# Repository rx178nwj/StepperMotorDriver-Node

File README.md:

# StepperMotorDriver-Node

NEMA17 用 / NEMA23 用のステッピングモータードライバー基板と、そのファームウェアのリポジトリです。
基板をモーター背面に取り付け、CAN バス経由で制御するノードとして使います。

## ディレクトリ構成

| パス | 内容 |
|------|------|
| `schematic_NEMA17/` | NEMA17 用基板の KiCad プロジェクト（回路図・基板・Gerber など） |
| `schematic_NEMA23/` | NEMA23 用基板の KiCad プロジェクト（回路図・基板・Gerber など） |
| `firmware/` | ファームウェア（STM32L433、CMake ベース。詳細は `firmware/README.md`） |
| `docs/` | ドキュメント |
| `datasheet/` | 部品データシート置き場（本体は含まない。`datasheet/README.md` 参照） |

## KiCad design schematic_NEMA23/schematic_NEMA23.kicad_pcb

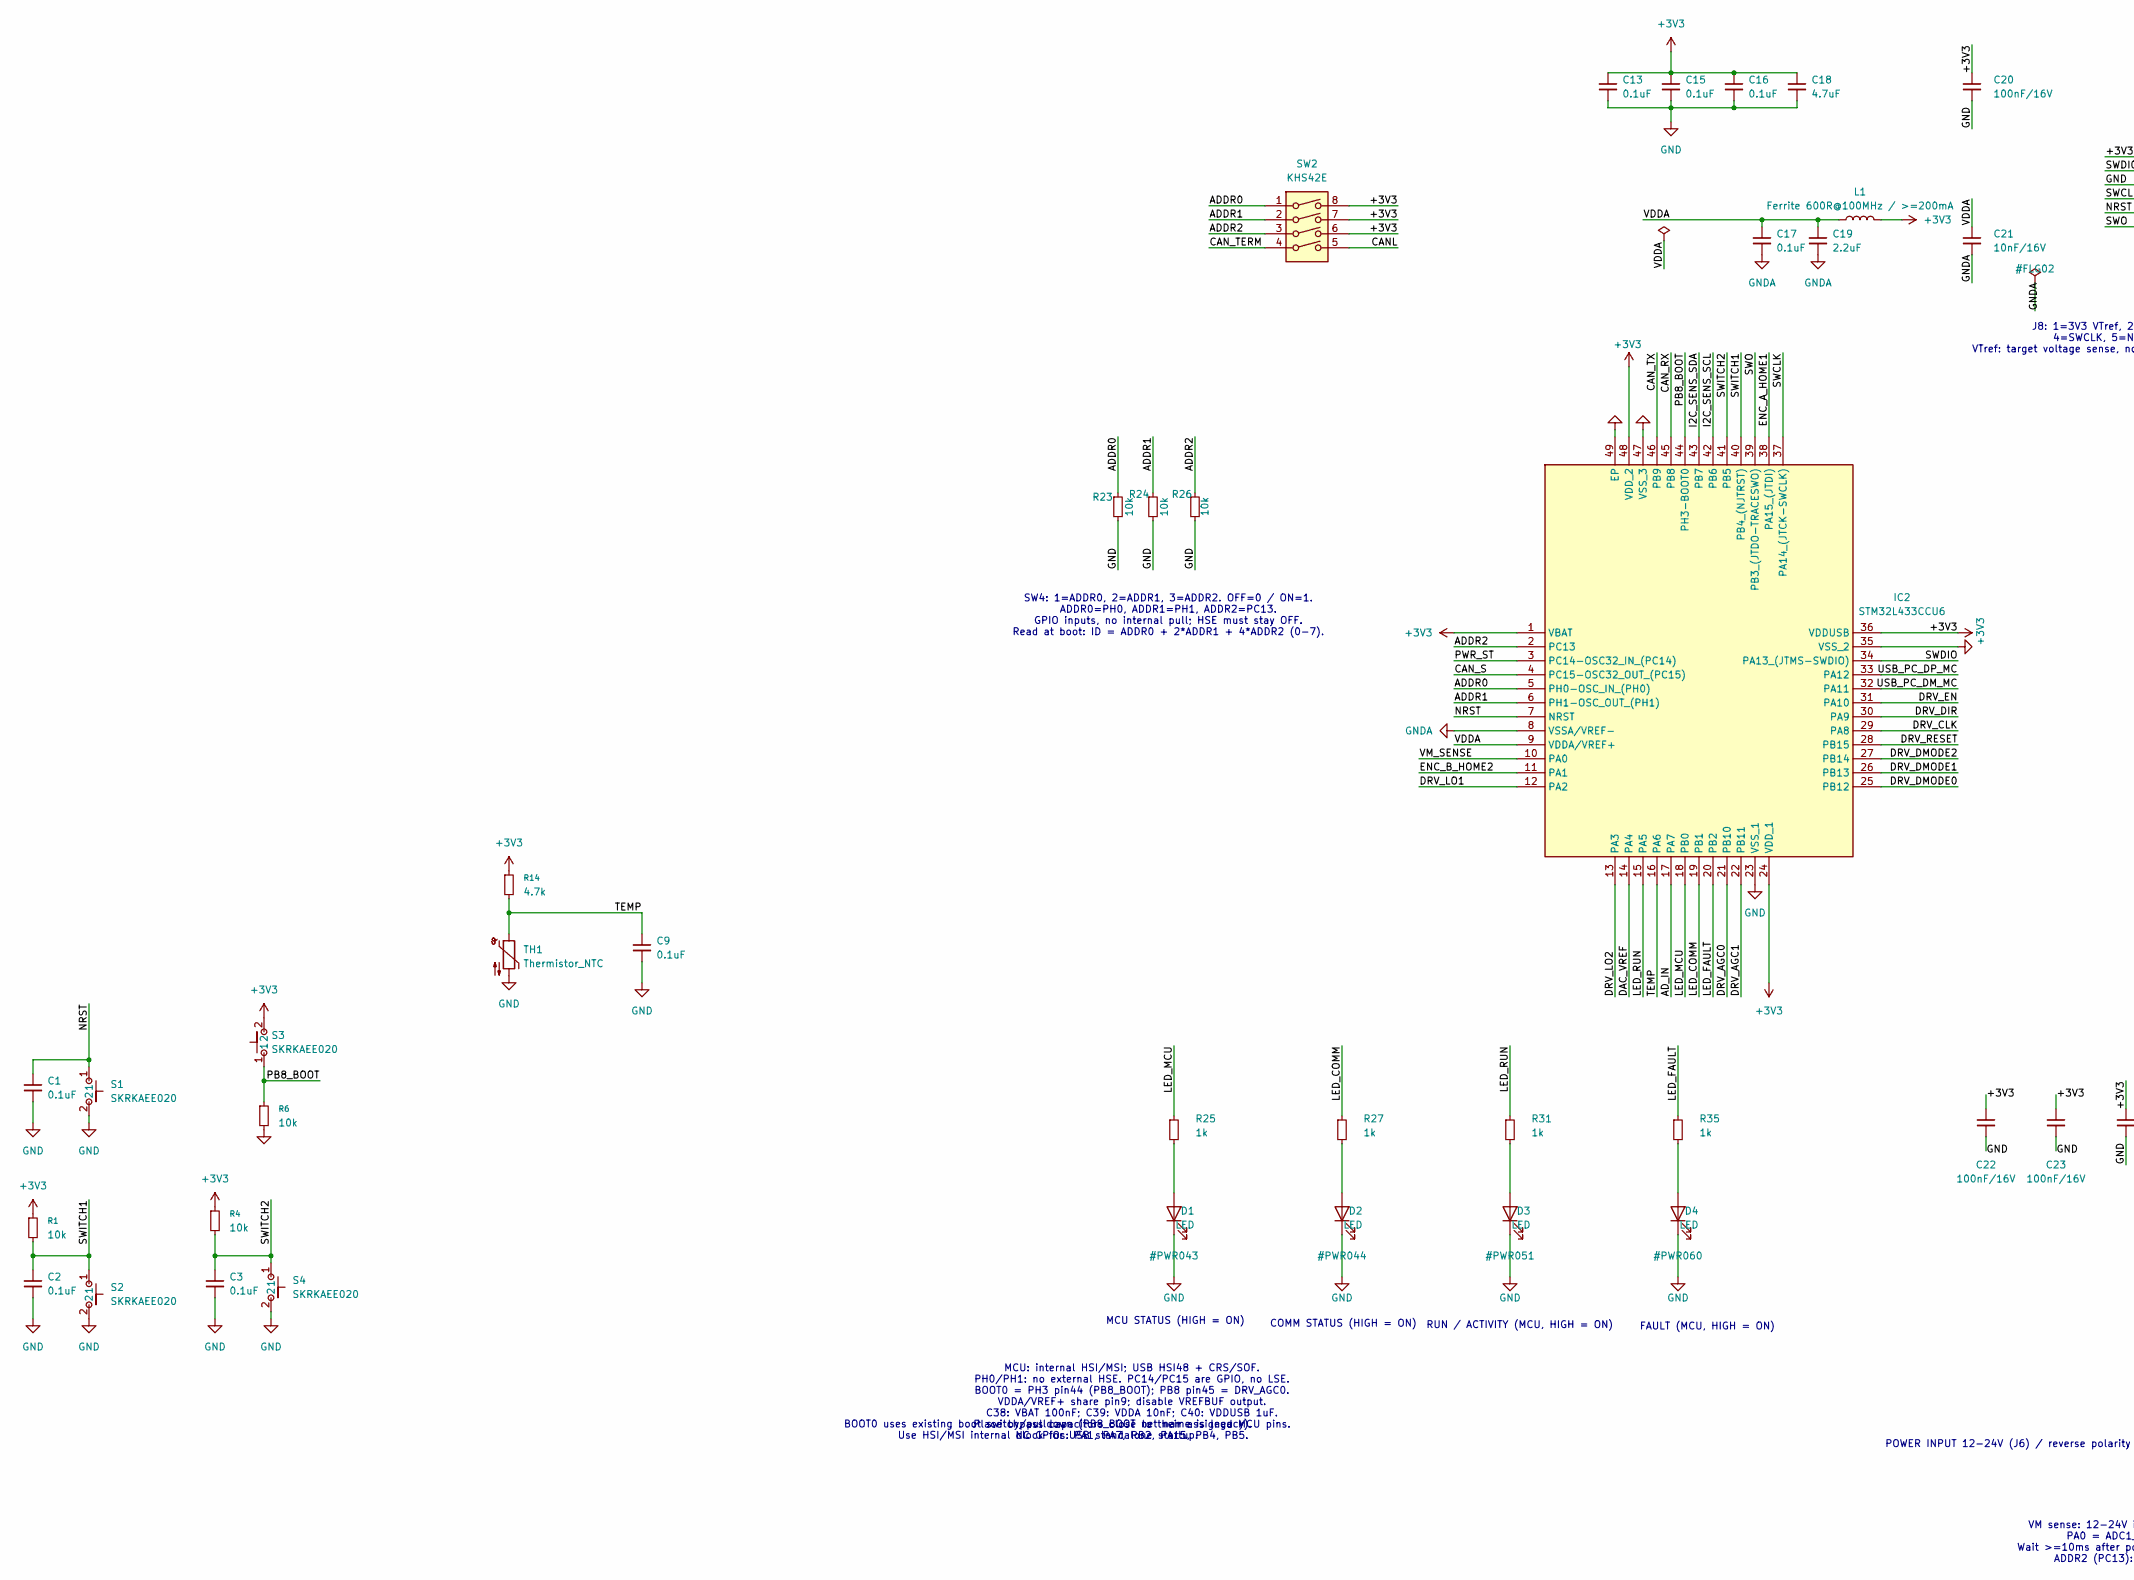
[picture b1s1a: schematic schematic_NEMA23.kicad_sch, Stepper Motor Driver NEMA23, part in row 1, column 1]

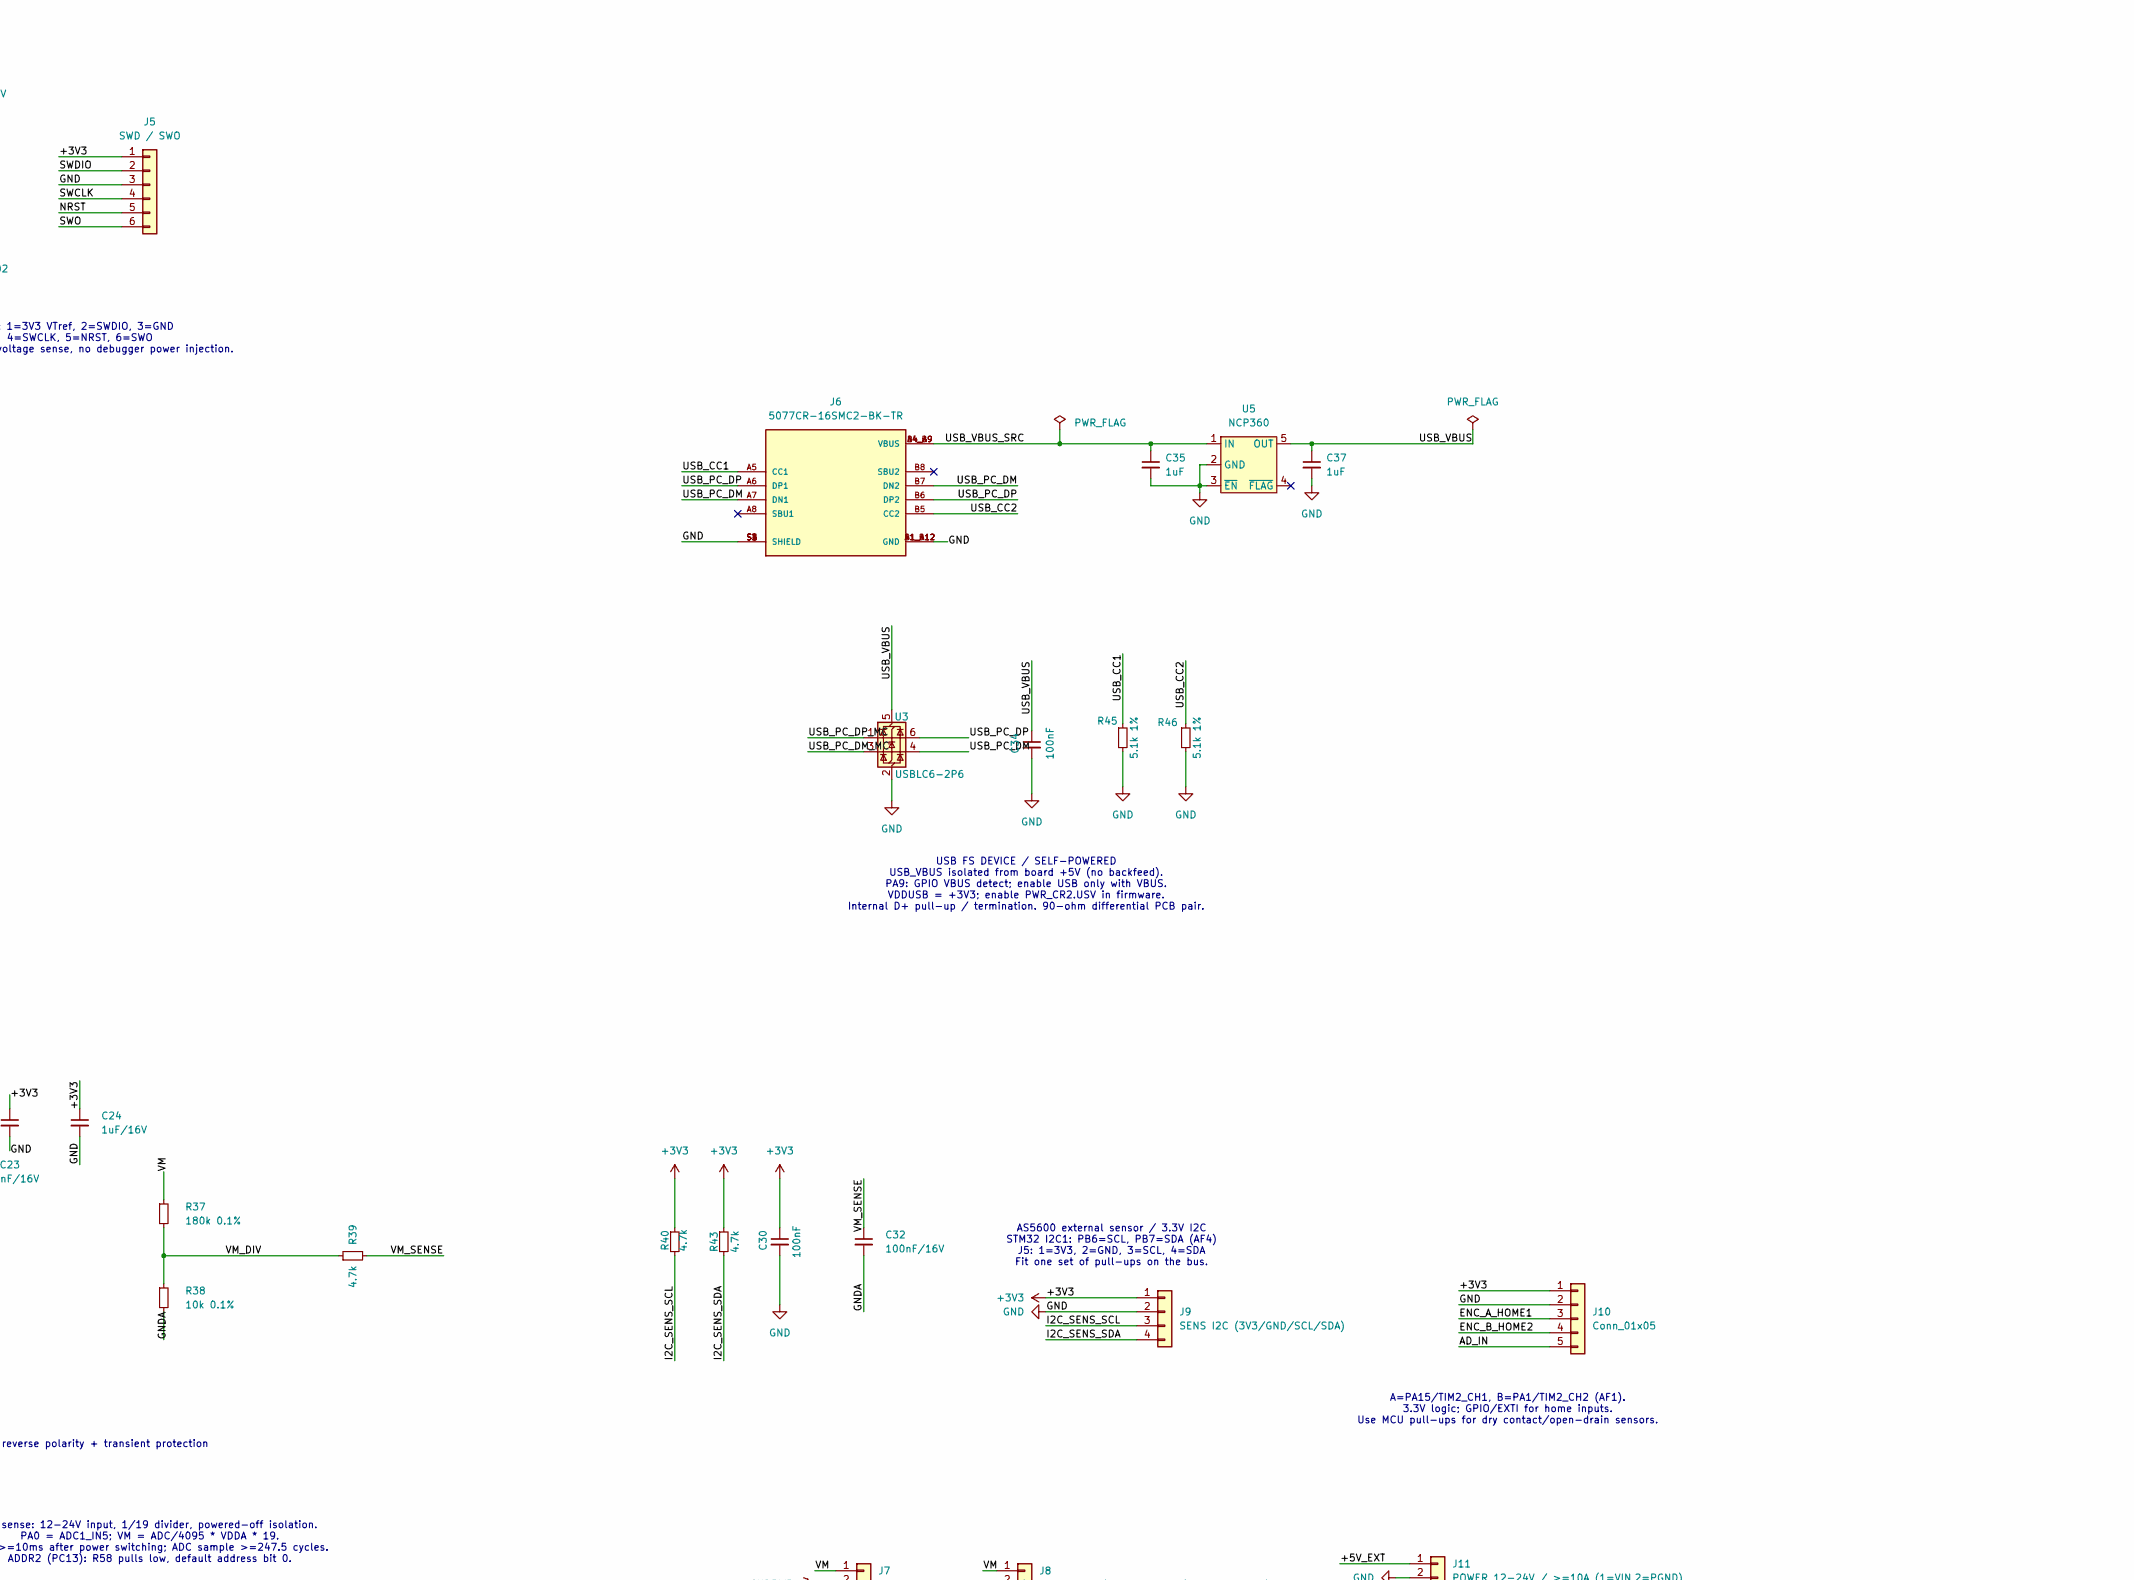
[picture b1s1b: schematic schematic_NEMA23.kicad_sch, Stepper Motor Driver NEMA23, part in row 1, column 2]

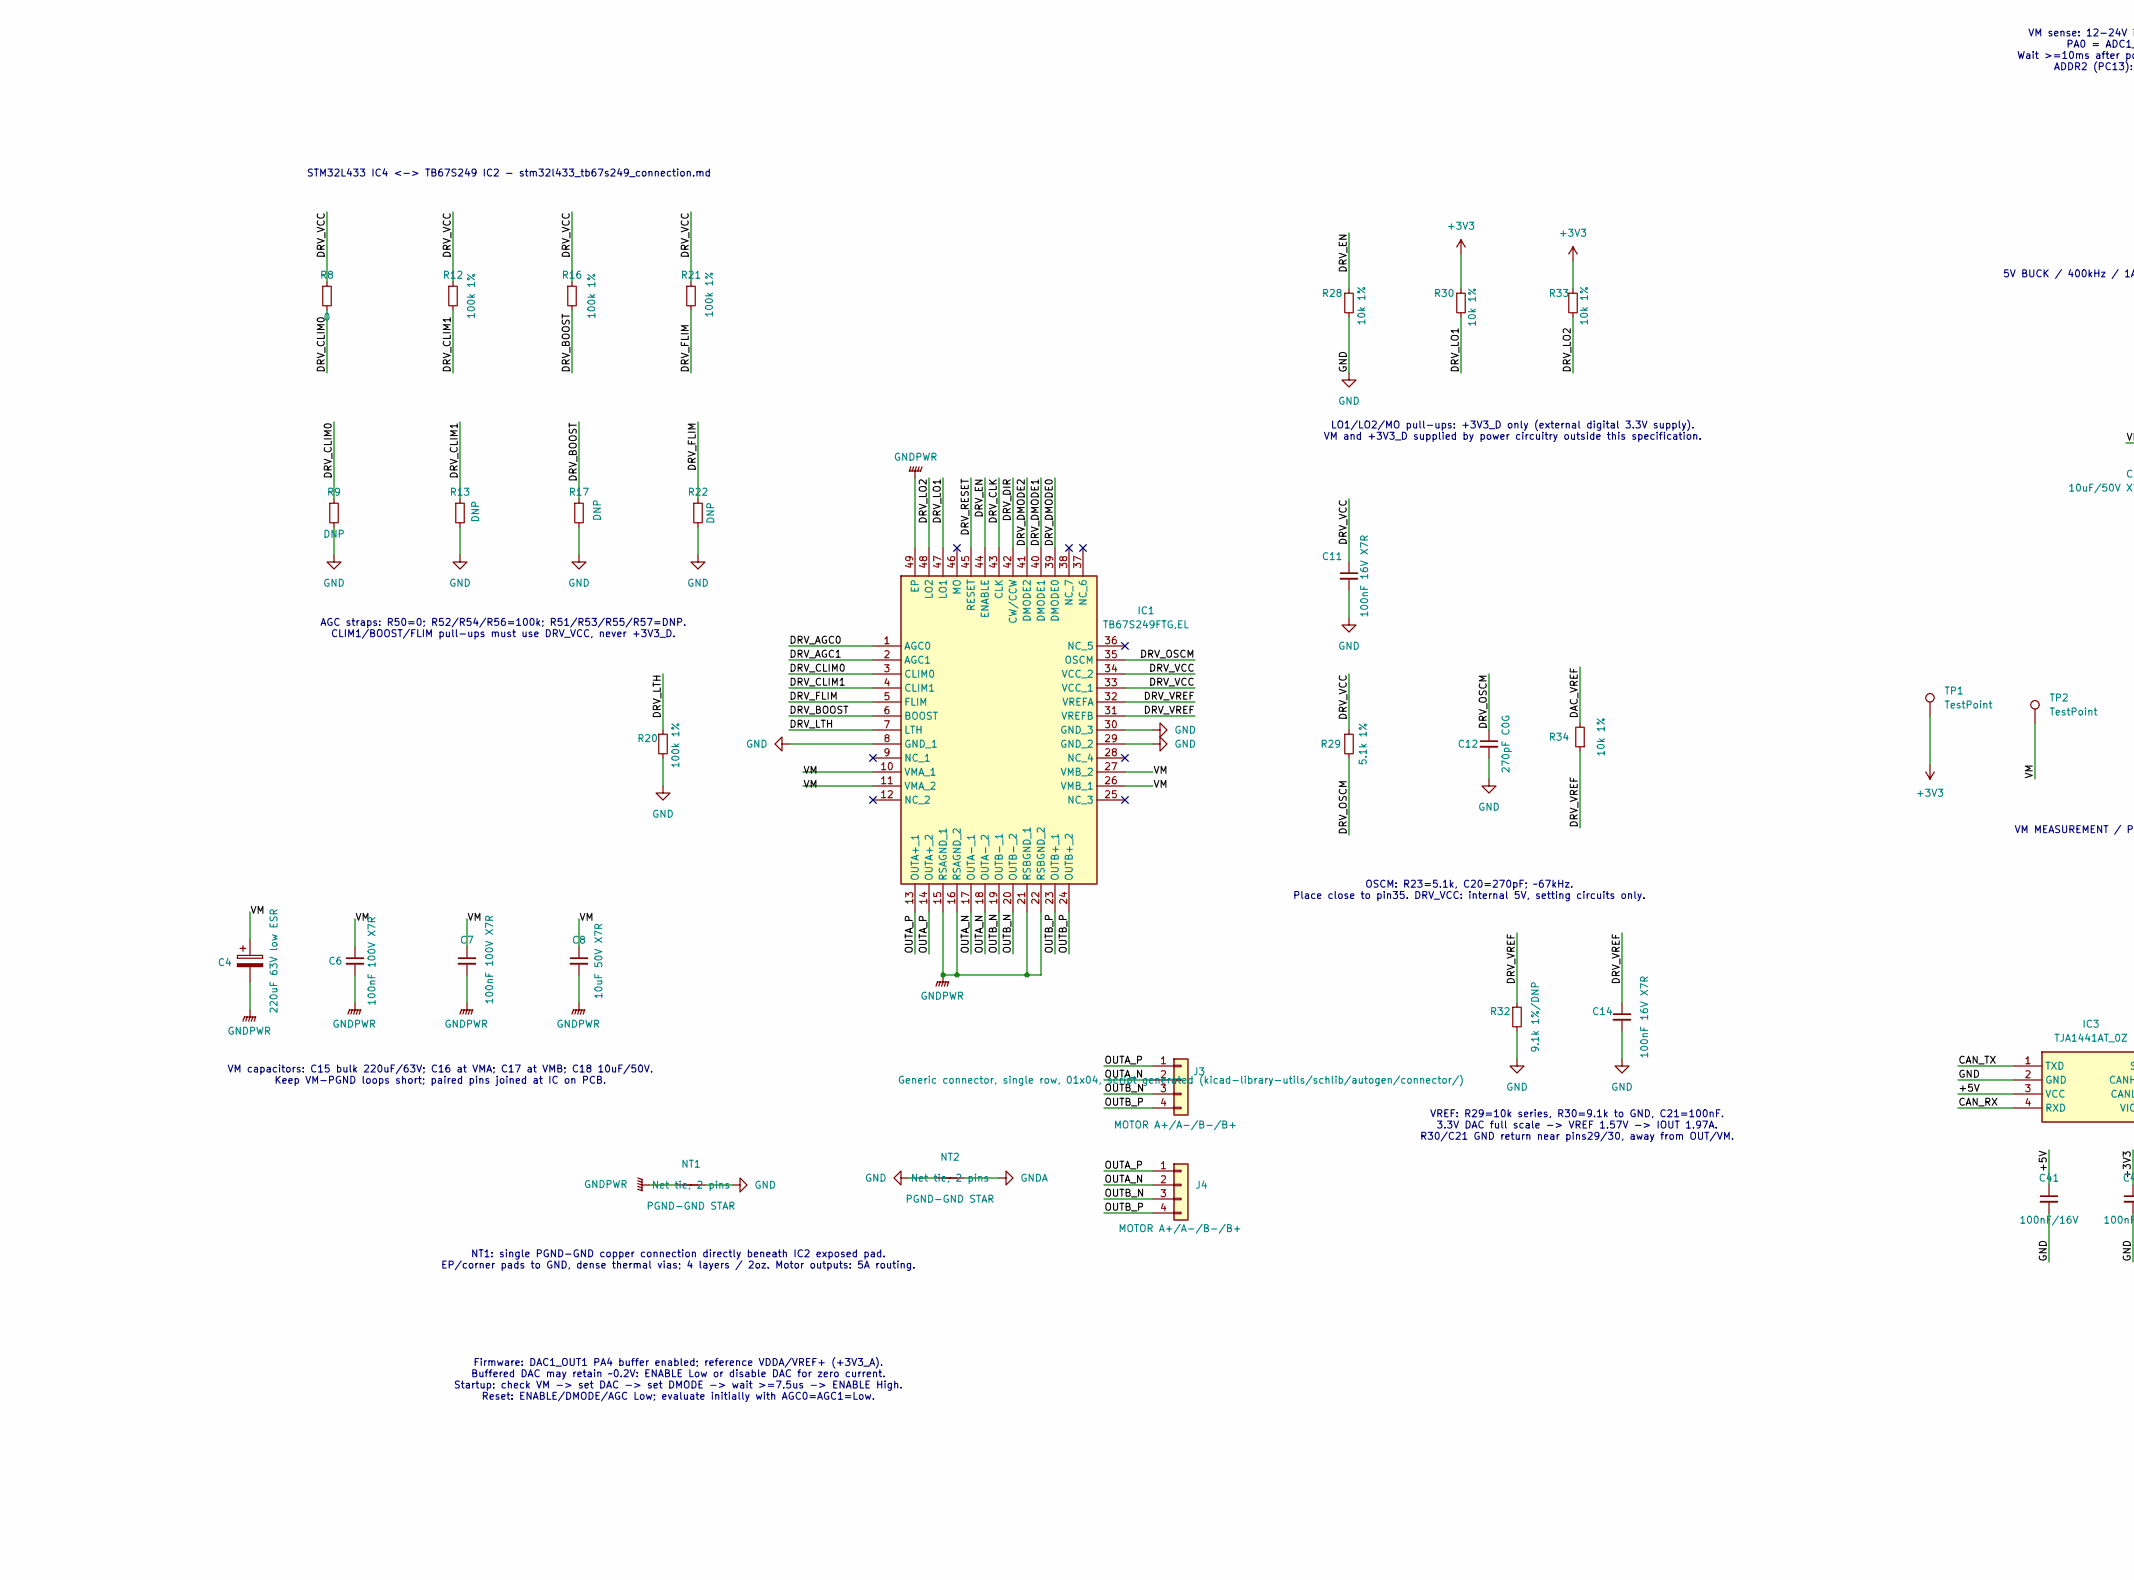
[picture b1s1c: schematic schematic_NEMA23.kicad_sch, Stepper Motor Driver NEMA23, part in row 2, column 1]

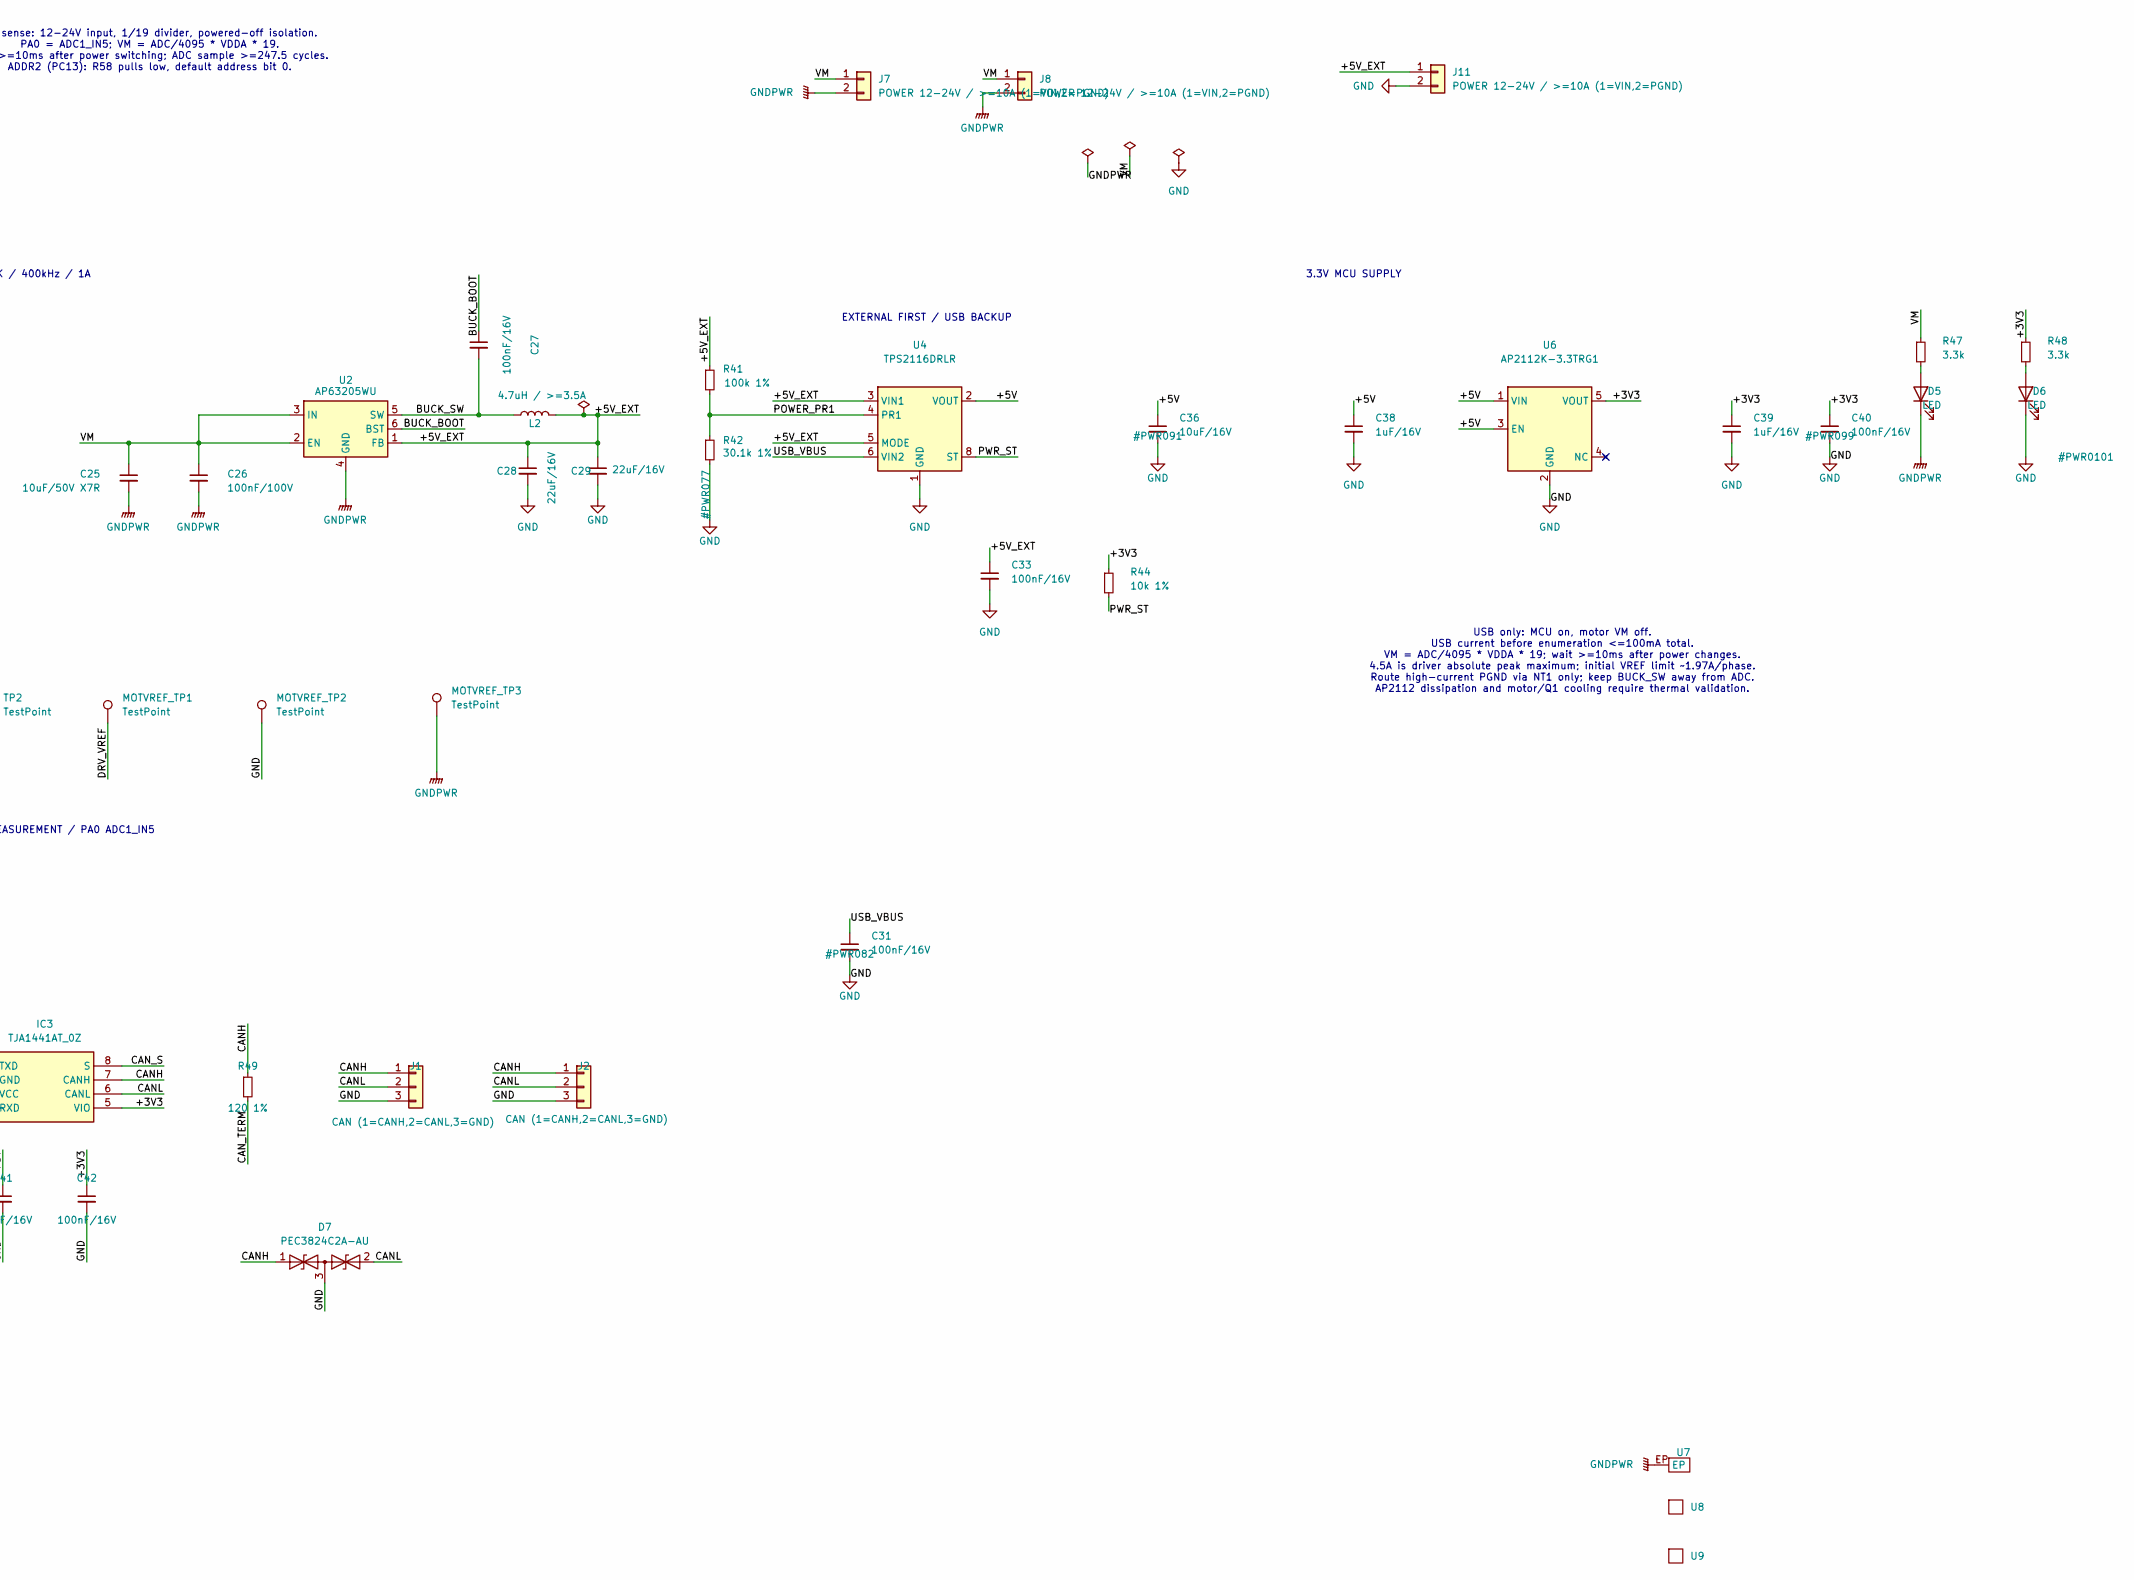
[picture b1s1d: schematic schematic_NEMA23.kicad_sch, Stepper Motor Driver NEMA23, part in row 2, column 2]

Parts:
C1, C2, C3, C9: 0.1uF; R_0402_1005Metric
C4: 220uF 63V low ESR; CP_Radial_D10.0mm_P5.00mm
C6, C7: 100nF 100V X7R; C_0603_1608Metric
C8: 10uF 50V X7R; C_0805_2012Metric
C11, C14: 100nF 16V X7R; C_0402_1005Metric
C12: 270pF C0G; C_0402_1005Metric
C13, C15, C16: 0.1uF; R_0603_1608Metric
C17: 0.1uF; C_0603_1608Metric
C18: 4.7uF; C_0805_2012Metric
C19: 2.2uF; C_0603_1608Metric
C20, C22, C23, C31, C33, C40: 100nF/16V; C_0603_1608Metric
C21: 10nF/16V; C_0603_1608Metric
C24, C38, C39: 1uF/16V; C_0603_1608Metric
C25: 10uF/50V X7R; C_0805_2012Metric; Voltage 50V
C26: 100nF/100V; C_0603_1608Metric
C27: 100nF/16V; C_0805_2012Metric
C28, C29: 22uF/16V; C_0805_2012Metric
C30, C34: 100nF; C_0603_1608Metric
C32: 100nF/16V; R_0402_1005Metric
C35, C37: 1uF; C_0603_1608Metric
C36: 10uF/16V; C_0805_2012Metric
C41, C42: 100nF/16V; C_0402_1005Metric
D1, D2, D3, D4, D5, D6: LED; LED_0603_1608Metric
D7: PEC3824C2A-AU; SOT-23
IC1: TB67S249FTG,EL; QFN50P700X700X100-49N-D; Mouser Part Number 757-TB67S249FTGEL
IC2: STM32L433CCU6; QFN50P700X700X60-49N-D; Mouser Part Number 511-STM32L433CCU6
IC3: TJA1441AT_0Z; SOIC127P600X175-8N; Mouser Part Number 771-TJA1441AT/0Z
J1, J2: CAN (1=CANH,2=CANL,3=GND); JST_PH_B3B-PH-K_1x03_P2.00mm_Vertical; MPN B3B-PH-K-S
J3: MOTOR A+/A-/B-/B+; JST_XH_B4B-XH-A_1x04_P2.50mm_Vertical
J4: MOTOR A+/A-/B-/B+; 名称未設定_1
J5: SWD / SWO; JST_ZH_B6B-ZR_1x06_P1.50mm_Vertical
J6: 5077CR-16SMC2-BK-TR; NELTRON_5077CR-16SMC2-BK-TR; PARTREV B
J7: POWER 12-24V / >=10A (1=VIN,2=PGND); Conn_VM
J8: POWER 12-24V / >=10A (1=VIN,2=PGND); JST_VH_B2P-VH_1x02_P3.96mm_Vertical
J9: SENS I2C (3V3/GND/SCL/SDA); JST_PH_B4B-PH-K_1x04_P2.00mm_Vertical
J10: Conn_01x05; JST_ZH_B5B-ZR_1x05_P1.50mm_Vertical
J11: POWER 12-24V / >=10A (1=VIN,2=PGND); JST_PH_B2B-PH-K_1x02_P2.00mm_Vertical
L1: Ferrite 600R@100MHz / >=200mA; L_0603_1608Metric
L2: 4.7uH / >=3.5A; INDPM5552X300N; MPN XAL6060-472MEC
MOTVREF_TP1, MOTVREF_TP2: TestPoint; TestPoint_THTPad_D2.0mm_Drill1.0mm
MOTVREF_TP3: TestPoint; TestPoint_Pad_D1.5mm
NT1, NT2: PGND-GND STAR; NetTie-2_SMD_Pad0.5mm
R1, R4, R6, R23, R24, R26: 10k; R_0402_1005Metric
R8: 0; R_0402_1005Metric
R9, R13, R17, R22: DNP; R_0402_1005Metric
R12, R16, R20, R21: 100k 1%; R_0402_1005Metric
R14, R39, R40, R43: 4.7k; R_0402_1005Metric
R25, R27, R31, R35: 1k; R_0603_1608Metric
R28, R30, R33, R34, R44: 10k 1%; R_0402_1005Metric
R29, R45, R46: 5.1k 1%; R_0402_1005Metric
R32: 9.1k 1%/DNP; R_0402_1005Metric
R37: 180k 0.1%; R_0603_1608Metric
R38: 10k 0.1%; R_0603_1608Metric
R41: 100k 1%; R_0603_1608Metric
R42: 30.1k 1%; R_0603_1608Metric
R47, R48: 3.3k; R_0603_1608Metric
R49: 120 1%; R_0603_1608Metric
S1, S2, S3, S4: SKRKAEE020; Mouser Part Number 688-SKRKAEE020
SW2: KHS42E; SOIC-8_5.3x6.2mm_P1.27mm
TH1: Thermistor_NTC; R_0603_1608Metric
TP1, TP2: TestPoint; TestPoint_Pad_D1.5mm
U2: AP63205WU; TSOT-23-6; MPN AP63205WU-7
U3: USBLC6-2P6; SOT-666
U4: TPS2116DRLR; SOT-583-8; MPN TPS2116DRLR
U5: NCP360; TSOP-5_1.65x3.05mm_P0.95mm
U6: AP2112K-3.3TRG1; SOT-23-5; MPN AP2112K-3.3TRG1
U7: サーマルパッド
U8: MainBoard
U9: ヒートシンク30x30

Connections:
+3V3: C13.1, C15.1, C16.1, C18.1, C20.1, C22.1, C23.1, C24.1, C30.1, C39.1, C40.1, C42.1, IC2.1 (VBAT), IC2.24 (VDD_1), IC2.36 (VDDUSB), IC2.48 (VDD_2), IC3.5 (VIO), J5.1, J9.1, J10.1, L1.2, R1.1, R4.1, R14.1, R30.1, R33.1, R40.1, R43.1, R44.1, R48.1, S3.2, SW2.6, SW2.7, SW2.8, TP1.1 (1_1), U6.5 (VOUT)
/+5V: C36.1, C38.1, C41.1, IC3.3 (VCC), U4.2 (VOUT), U4.7 (VOUT), U6.1 (VIN), U6.3 (EN)
/+5V_EXT: C28.1, C29.1, C33.1, J11.1, L2.2, R41.1, U2.1 (FB), U4.3 (VIN1), U4.5 (MODE)
/ADDR0: IC2.5 (PH0-OSC_IN_(PH0)), R23.1, SW2.1
/ADDR1: IC2.6 (PH1-OSC_OUT_(PH1)), R24.1, SW2.2
/ADDR2: IC2.2 (PC13), R26.1, SW2.3
/AD_IN: IC2.17 (PA7), J10.5
/BUCK_BOOT: C27.1, U2.6 (BST)
/BUCK_SW: C27.2, L2.1, U2.5 (SW)
/CANH: D7.1 (A1), IC3.7 (CANH), J1.1, J2.1, R49.1
/CANL: D7.2 (A2), IC3.6 (CANL), J1.2, J2.2, SW2.5
/CAN_RX: IC2.45 (PB8), IC3.4 (RXD)
/CAN_S: IC2.4 (PC15-OSC32_OUT_(PC15)), IC3.8 (S)
/CAN_TERM: R49.2, SW2.4
/CAN_TX: IC2.46 (PB9), IC3.1 (TXD)
/DAC_VREF: IC2.14 (PA4), R34.2
/DRV_AGC0: IC1.1 (AGC0), IC2.21 (PB10)
/DRV_AGC1: IC1.2 (AGC1), IC2.22 (PB11)
/DRV_BOOST: IC1.6 (BOOST), R16.2, R17.1
/DRV_CLIM0: IC1.3 (CLIM0), R8.2, R9.1
/DRV_CLIM1: IC1.4 (CLIM1), R12.2, R13.1
/DRV_CLK: IC1.43 (CLK), IC2.29 (PA8)
/DRV_DIR: IC1.42 (CW/CCW), IC2.30 (PA9)
/DRV_DMODE0: IC1.39 (DMODE0), IC2.25 (PB12)
/DRV_DMODE1: IC1.40 (DMODE1), IC2.26 (PB13)
/DRV_DMODE2: IC1.41 (DMODE2), IC2.27 (PB14)
/DRV_EN: IC1.44 (ENABLE), IC2.31 (PA10), R28.1
/DRV_FLIM: IC1.5 (FLIM), R21.2, R22.1
/DRV_LO1: IC1.47 (LO1), IC2.12 (PA2), R30.2
/DRV_LO2: IC1.48 (LO2), IC2.13 (PA3), R33.2
/DRV_LTH: IC1.7 (LTH), R20.1
/DRV_OSCM: C12.1, IC1.35 (OSCM), R29.2
/DRV_RESET: IC1.45 (RESET), IC2.28 (PB15)
/DRV_VCC: C11.1, IC1.33 (VCC_1), IC1.34 (VCC_2), R8.1, R12.1, R16.1, R21.1, R29.1
/DRV_VREF: C14.1, IC1.31 (VREFB), IC1.32 (VREFA), MOTVREF_TP1.1 (1_1), R32.1, R34.1
/ENC_A_HOME1: IC2.38 (PA15_(JTDI)), J10.3
/ENC_B_HOME2: IC2.11 (PA1), J10.4
/I2C_SENS_SCL: IC2.42 (PB6), J9.3, R40.2
/I2C_SENS_SDA: IC2.43 (PB7), J9.4, R43.2
/LED_COMM: IC2.19 (PB1), R27.1
/LED_FAULT: IC2.20 (PB2), R35.1
/LED_MCU: IC2.18 (PB0), R25.1
/LED_RUN: IC2.15 (PA5), R31.1
/NRST: C1.1, IC2.7 (NRST), J5.5, S1.1
/OUTA_N: IC1.17 (OUTA-_1), IC1.18 (OUTA-_2), J3.2, J4.2
/OUTA_P: IC1.13 (OUTA+_1), IC1.14 (OUTA+_2), J3.1, J4.1
/OUTB_N: IC1.19 (OUTB-_1), IC1.20 (OUTB-_2), J3.3, J4.3
/OUTB_P: IC1.23 (OUTB+_1), IC1.24 (OUTB+_2), J3.4, J4.4
/PB8_BOOT: IC2.44 (PH3-BOOT0), R6.1, S3.1
/POWER_PR1: R41.2, R42.1, U4.4 (PR1)
/PWR_ST: IC2.3 (PC14-OSC32_IN_(PC14)), R44.2, U4.8 (ST)
/SWCLK: IC2.37 (PA14_(JTCK-SWCLK)), J5.4
/SWDIO: IC2.34 (PA13_(JTMS-SWDIO)), J5.2
/SWITCH1: C2.1, IC2.40 (PB4_(NJTRST)), R1.2, S2.1
/SWITCH2: C3.1, IC2.41 (PB5), R4.2, S4.1
/SWO: IC2.39 (PB3_(JTDO-TRACESWO)), J5.6
/TEMP: C9.1, IC2.16 (PA6), R14.2, TH1.1
/USB_CC1: J6.A5 (CC1), R45.1
/USB_CC2: J6.B5 (CC2), R46.1
/USB_PC_DM: J6.A7 (DN1), J6.B7 (DN2), U3.4 (I/O2)
/USB_PC_DM_MC: IC2.32 (PA11), U3.3 (I/O2)
/USB_PC_DP: J6.A6 (DP1), J6.B6 (DP2), U3.6 (I/O1)
/USB_PC_DP_MC: IC2.33 (PA12), U3.1 (I/O1)
/USB_VBUS: C31.1, C34.1, C37.1, U3.5 (VBUS), U4.6 (VIN2), U5.5 (OUT)
/USB_VBUS_SRC: C35.1, J6.A4_B9 (VBUS), J6.B4_A9 (VBUS), U5.1 (IN)
/VDDA: C17.1, C19.1, C21.1, IC2.9 (VDDA/VREF+), L1.1
/VM: C4.1, C6.1, C7.1, C8.1, C25.1, C26.1, IC1.10 (VMA_1), IC1.11 (VMA_2), IC1.26 (VMB_1), IC1.27 (VMB_2), J7.1, J8.1, R37.1, R47.1, TP2.1 (1_1), U2.2 (EN), U2.3 (IN)
/VM_DIV: R37.2, R38.1, R39.1
/VM_SENSE: C32.1, IC2.10 (PA0), R39.2
GND: C1.2, C2.2, C3.2, C9.2, C11.2, C12.2, C13.2, C14.2, C15.2, C16.2, C18.2, C20.2, C22.2, C23.2, C24.2, C28.2, C29.2, C30.2, C31.2, C33.2, C34.2, C35.2, C36.2, C37.2, C38.2, C39.2, C40.2, C41.2, C42.2, D1.1 (K), D2.1 (K), D3.1 (K), D4.1 (K), D6.1 (K), D7.3 (common), IC1.8 (GND_1), IC1.29 (GND_2), IC1.30 (GND_3), IC2.23 (VSS_1), IC2.35 (VSS_2), IC2.47 (VSS_3), IC2.49 (EP), IC3.2 (GND), J1.3, J2.3, J5.3, J6.A1_B12 (GND), J6.B1_A12 (GND), J6.S1 (SHIELD), J6.S2 (SHIELD), J6.S3 (SHIELD), J6.S4 (SHIELD), J9.2, J10.2, J11.2, MOTVREF_TP2.1 (1_1), NT1.2, NT2.1, R6.2, R9.2, R13.2, R17.2, R20.2, R22.2, R23.2, R24.2, R26.2, R28.2, R32.2, R42.2, R45.2, R46.2, S1.2, S2.2, S4.2, TH1.2, U3.2 (GND), U4.1 (GND), U5.2 (GND), U5.3 (~EN), U6.2 (GND)
GNDA: C17.2, C19.2, C21.2, C32.2, IC2.8 (VSSA/VREF-), NT2.2, R38.2
GNDPWR: C4.2, C6.2, C7.2, C8.2, C25.2, C26.2, D5.1 (K), IC1.15 (RSAGND_1), IC1.16 (RSAGND_2), IC1.21 (RSBGND_1), IC1.22 (RSBGND_2), IC1.49 (EP), J7.2, J8.2, MOTVREF_TP3.1 (1_1), NT1.1, U2.4 (GND), U7.EP (EP_EP)
unnamed: D1.2 (A), R25.2
unnamed: D2.2 (A), R27.2
unnamed: D3.2 (A), R31.2
unnamed: D4.2 (A), R35.2
unnamed: D5.2 (A), R47.2
unnamed: D6.2 (A), R48.2

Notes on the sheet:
COMM STATUS (HIGH = ON)
LO1/LO2/MO pull-ups: +3V3_D only (external digital 3.3V supply). VM and +3V3_D supplied by power circuitry outside this specification.
NT1: single PGND-GND copper connection directly beneath IC2 exposed pad. EP/corner pads to GND, dense thermal vias; 4 layers / 2oz. Motor outputs: 5A routing.
POWER INPUT 12-24V (J6) / reverse polarity + transient protection
SW4: 1=ADDR0, 2=ADDR1, 3=ADDR2. OFF=0 / ON=1. ADDR0=PH0, ADDR1=PH1, ADDR2=PC13. GPIO inputs, no internal pull; HSE must stay OFF. Read at boot: ID = ADDR0 + 2*ADDR1 + 4*ADDR2 (0-7).
USB only: MCU on, motor VM off. USB current before enumeration <=100mA total. VM = ADC/4095 * VDDA * 19; wait >=10ms after power changes. 4.5A is driver absolute peak maximum; initial VREF limit ~1.97A/phase. Route high-current PGND via NT1 only; keep BUCK_SW away from ADC. AP2112 dissipation and m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
MCU STATUS (HIGH = ON)
AGC straps: R50=0; R52/R54/R56=100k; R51/R53/R55/R57=DNP. CLIM1/BOOST/FLIM pull-ups must use DRV_VCC, never +3V3_D.
USB FS DEVICE / SELF-POWERED USB_VBUS isolated from board +5V (no backfeed). PA9: GPIO VBUS detect; enable USB only with VBUS. VDDUSB = +3V3; enable PWR_CR2.USV in firmware. Internal D+ pull-up / termination. 90-ohm differential PCB pair.
OSCM: R23=5.1k, C20=270pF; ~67kHz. Place close to pin35. DRV_VCC: internal 5V, setting circuits only.
5V BUCK / 400kHz / 1A
STM32L433 IC4 <-> TB67S249 IC2 - stm32l433_tb67s249_connection.md
EXTERNAL FIRST / USB BACKUP
3.3V MCU SUPPLY
VREF: R29=10k series, R30=9.1k to GND, C21=100nF. 3.3V DAC full scale -> VREF 1.57V -> IOUT 1.97A. R30/C21 GND return near pins29/30, away from OUT/VM.
RUN / ACTIVITY (MCU, HIGH = ON)
BOOT0 uses existing boot switch/pulldown (PB8_BOOT net name is legacy). Use HSI/MSI internal clock for USB standalone startup.
A=PA15/TIM2_CH1, B=PA1/TIM2_CH2 (AF1). 3.3V logic; GPIO/EXTI for home inputs. Use MCU pull-ups for dry contact/open-drain sensors.
AS5600 external sensor / 3.3V I2C STM32 I2C1: PB6=SCL, PB7=SDA (AF4) J5: 1=3V3, 2=GND, 3=SCL, 4=SDA Fit one set of pull-ups on the bus.
J8: 1=3V3 VTref, 2=SWDIO, 3=GND 4=SWCLK, 5=NRST, 6=SWO VTref: target voltage sense, no debugger power injection.
FAULT (MCU, HIGH = ON)
MCU: internal HSI/MSI; USB HSI48 + CRS/SOF. PH0/PH1: no external HSE. PC14/PC15 are GPIO, no LSE. BOOT0 = PH3 pin44 (PB8_BOOT); PB8 pin45 = DRV_AGC0. VDDA/VREF+ share pin9; disable VREFBUF output. C38: VBAT 100nF; C39: VDDA 10nF; C40: VDDUSB 1uF. Place bypass capacitors close to their assigned MCU 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
Firmware: DAC1_OUT1 PA4 buffer enabled; reference VDDA/VREF+ (+3V3_A). Buffered DAC may retain ~0.2V: ENABLE Low or disable DAC for zero current. Startup: check VM -> set DAC -> set DMODE -> wait >=7.5us -> ENABLE High. Reset: ENABLE/DMODE/AGC Low; evaluate initially with AGC0=AGC1=Low.
VM sense: 12-24V input, 1/19 divider, powered-off isolation. PA0 = ADC1_IN5; VM = ADC/4095 * VDDA * 19. Wait >=10ms after power switching; ADC sample >=247.5 cycles. ADDR2 (PC13): R58 pulls low, default address bit 0.
VM capacitors: C15 bulk 220uF/63V; C16 at VMA; C17 at VMB; C18 10uF/50V. Keep VM-PGND loops short; paired pins joined at IC on PCB.
VM MEASUREMENT / PA0 ADC1_IN5

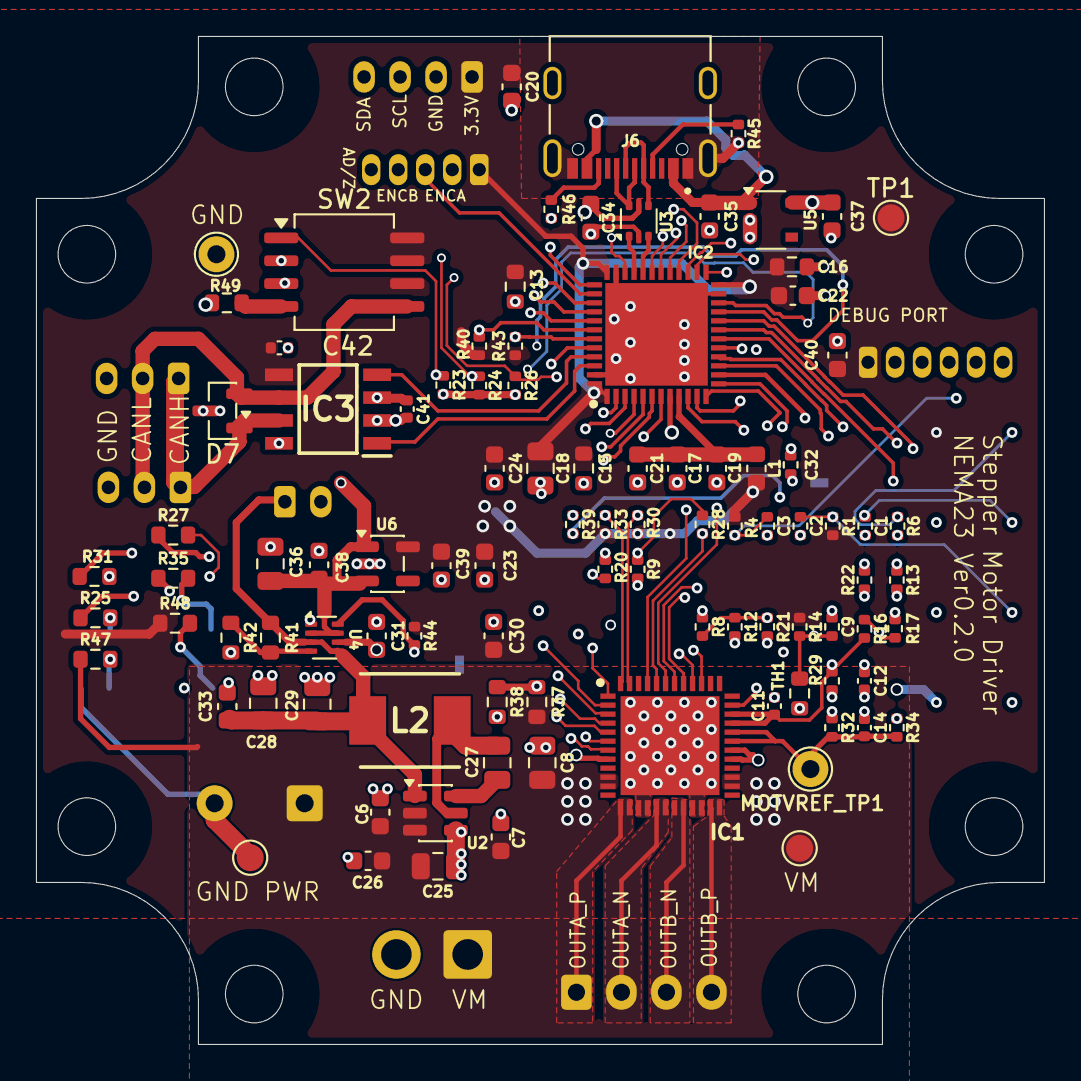
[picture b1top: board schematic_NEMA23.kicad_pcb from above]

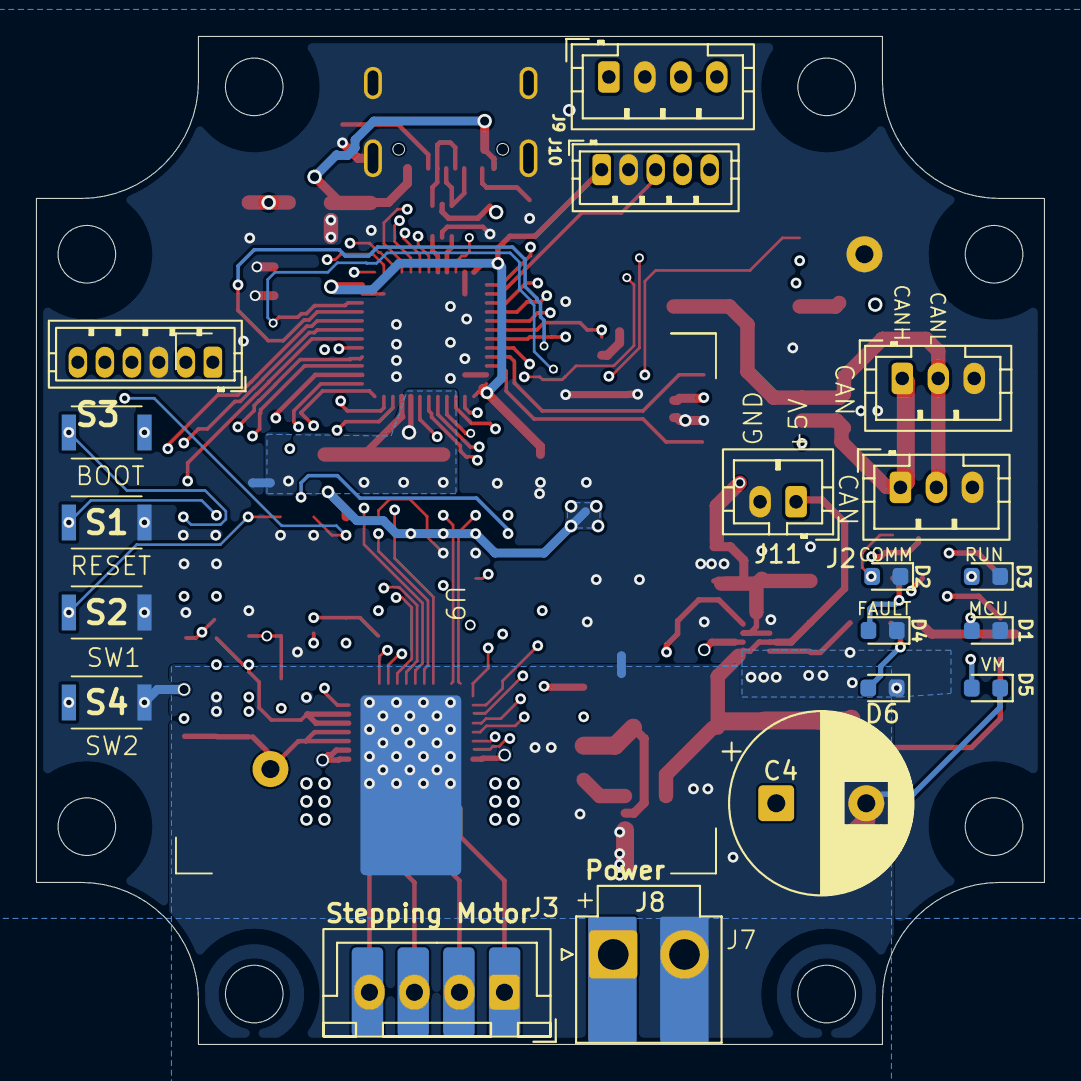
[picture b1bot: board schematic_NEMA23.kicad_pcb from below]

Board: 4 copper layers, 56.0 x 56.0 mm, 123 parts (25 on the bottom side), 78 nets.
